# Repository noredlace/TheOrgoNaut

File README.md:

# TheOrgoNaut66

A design by u/lizardsticks

A an ergonomic ortholinear 60% board. Inspiration from the atreus with a twist on the modifiers and keys to fit most keycap designs. <br /> 

Nonstandard keycaps include the 2.25u Novelty on the left side. This keycap is meant to be used with either the Enter Key or a Novelty Enter Key. 

The left shift key was chosen to be a 2.75u with the right shift being a split shift 1.75u + 1u key.

I suppose the inner column 1u keycaps for 5,3 nd 5,4 could potentially be difficult to find, in the meantime the numpad of a keycap set should suffice.

This allows the keyboard to be symmetrical while having good compatibility with most base keycap sets.

KLE

The color code helps identify the rows of diodes that will be used. The spacing allows for me to visualize the columns. The actual PCB won't have the spacing that you see on the left and right side. The triangle spacing in the middle will stay.

Before this, I had made the matrix based off the position of keys, which made tracing messy due to a multitude of crossed traces. Thus I made necessary changes to allow for cleaner traces and minimal vias.

You can also see the row and column numbers to visualize the schematic.

Schematic was done in a 9 x 8 layout. This is due to the 66 keys on the OrgoNaut. <br />

PCB Dimensions are 148x362mm(5.81x14.25 inches) 
Front PCB

Back PCB

As you can see in the photos, the pcb is relatively clean in terms of the tracing. Of course its relative to how much of a mess my previous trace attempts have been.

Update v2 attempted to create aesthetically pleasing tracing. significant focus on how tracing to the pro micro 

Update v3 changed the pictures from KiCad's renderer to a gerber viewer provided by EasyEDA

Update v4 brought uniform ground planes to cover both front and back of the pcb. As well as changing the through hole footprints from m2 screw holes to pok3r style holes

# Major Update
The PCBs have been ordered and delivered courtesy of EasyEDA. The PCBs have been tested and all holes are currently registering correct keystrokes for the simple keyboard layout that has been made.

PCBs just delivered

PCB Soldered with diodes and socketed pro micro

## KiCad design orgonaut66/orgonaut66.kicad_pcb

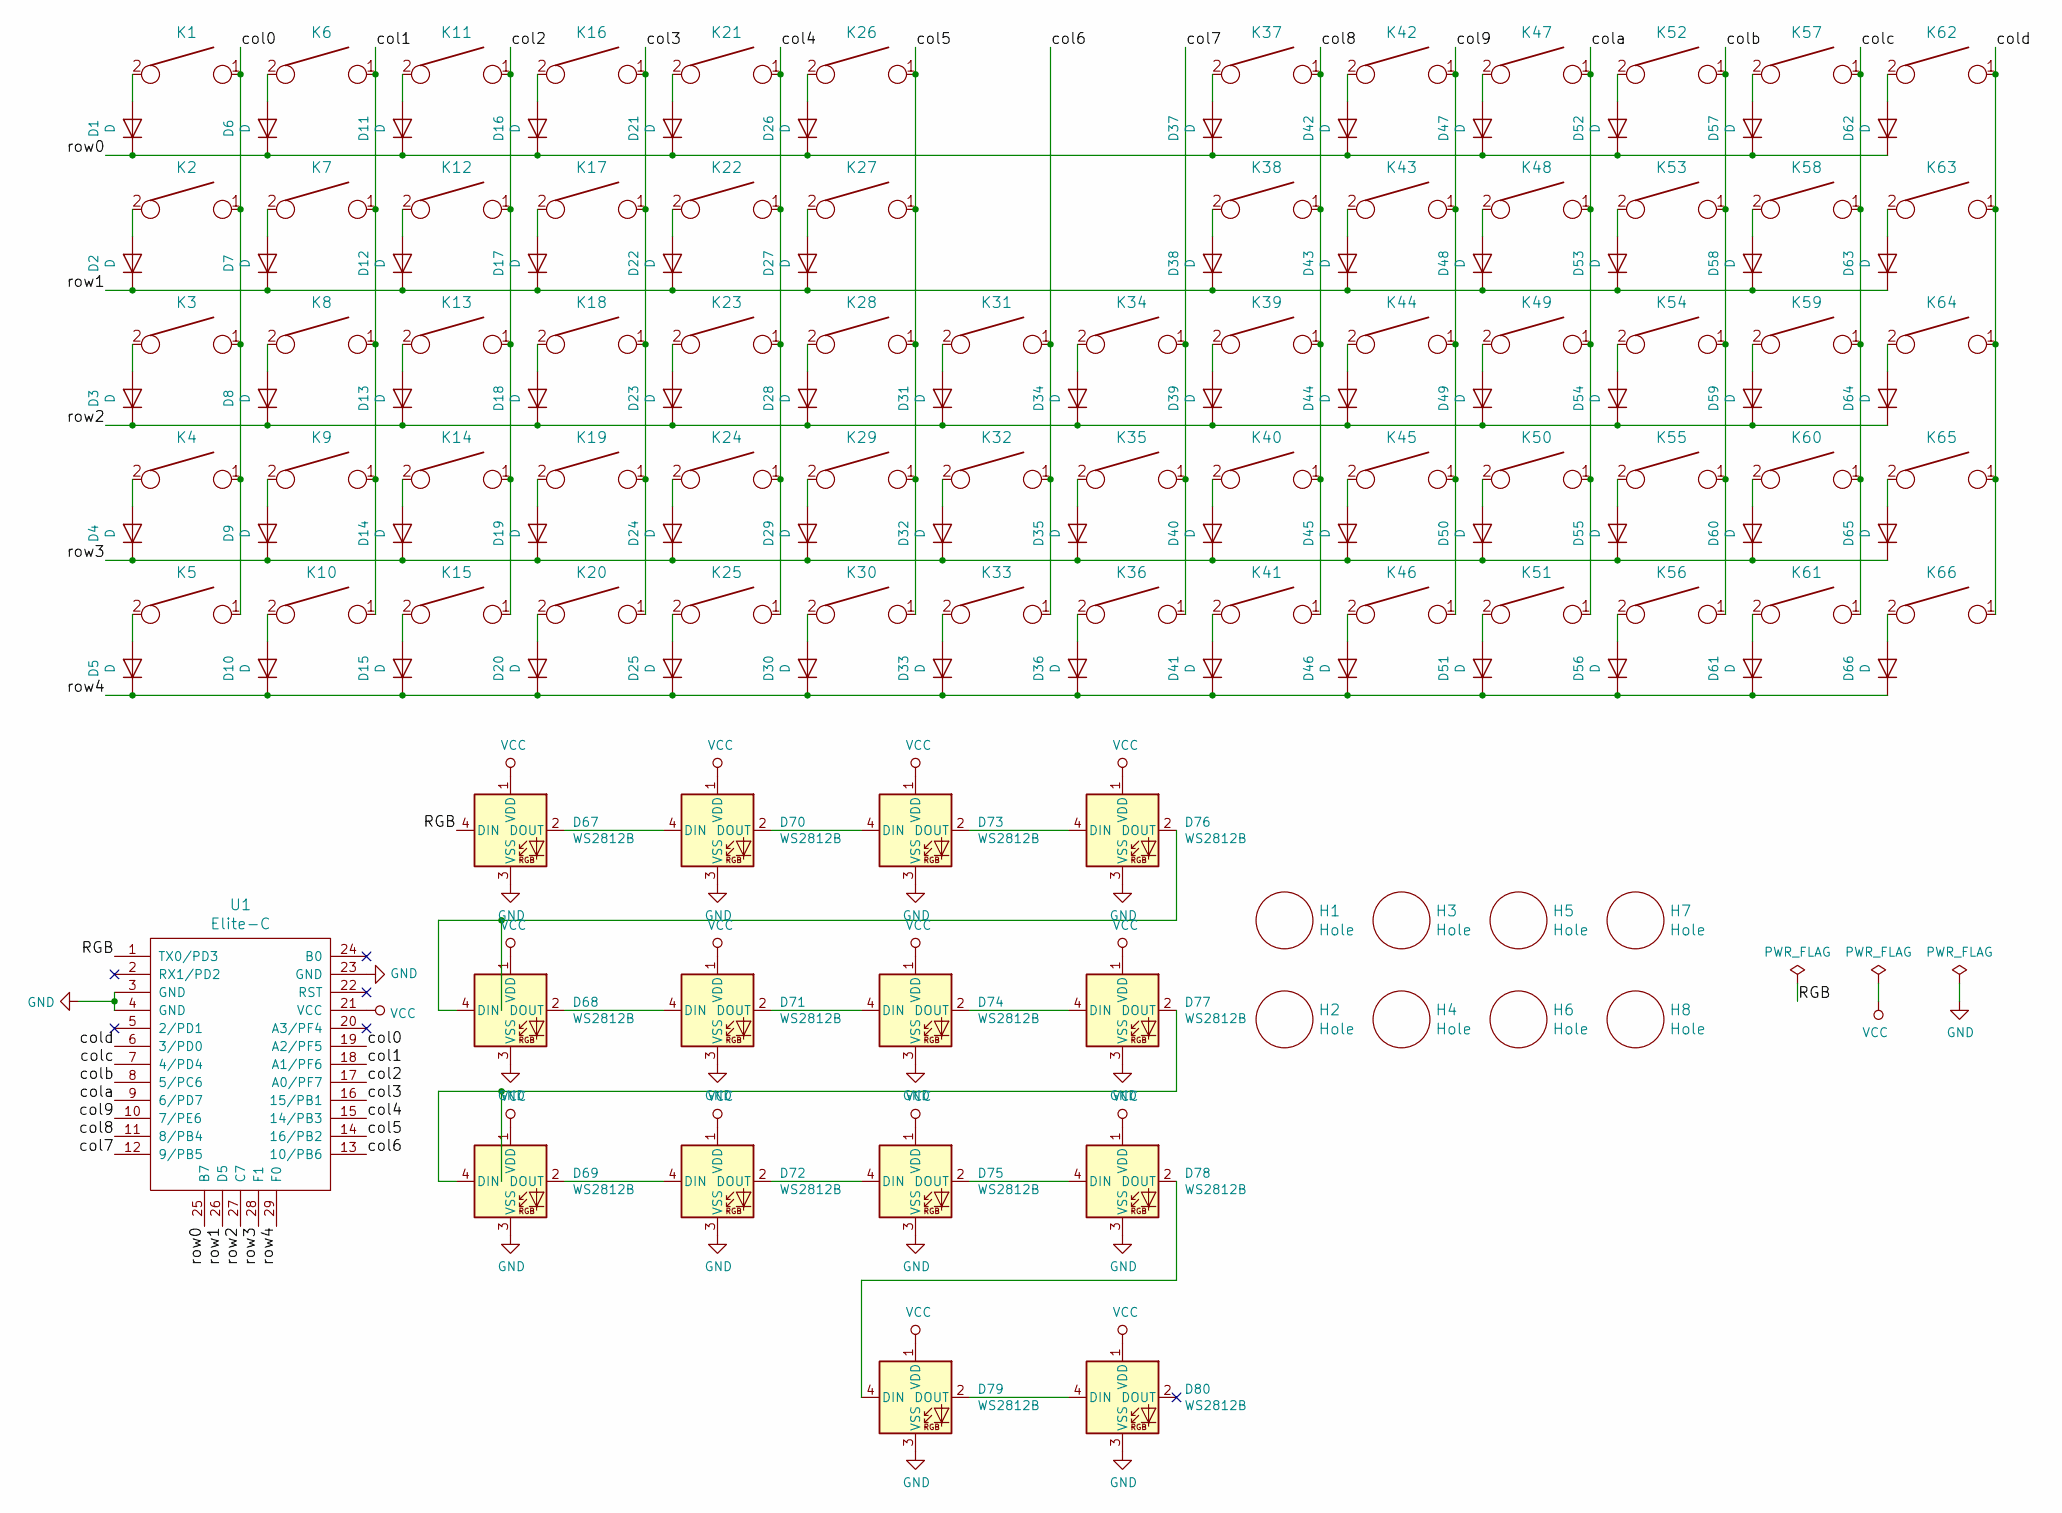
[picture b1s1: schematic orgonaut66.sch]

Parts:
D1, D2, D3, D4, D5, D6, D7, D8, D9, D10, D11, D12, D13, D14, D15, D16, D17, D18, D19, D20, D21, D22, D23, D24, D25, D26, D27, D28, D29, D30, D31, D32, D33, D34, D35, D36, D37, D38, D39, D40, D41, D42, D43, D44, D45, D46, D47, D48, D49, D50, D51, D52, D53, D54, D55, D56, D57, D58, D59, D60, D61, D62, D63, D64, D65, D66: D; D_SOD123_ThroughHole
D67, D68, D69, D70, D71, D72, D73, D74, D75, D76, D77, D78, D79, D80: WS2812B; RGBW_LED_5mm
H1, H2, H3, H4, H5, H6, H7, H8: Hole; Poker_oval_hole
K1, K2, K6, K7, K8, K9, K10, K11, K12, K13, K14, K15, K16, K17, K18, K19, K20, K21, K22, K23, K24, K25, K26, K27, K28, K29, K30, K31, K32, K34, K35, K37, K38, K39, K40, K41, K42, K43, K44, K45, K46, K47, K48, K49, K50, K51, K52, K53, K54, K55, K56, K57, K58, K59, K60, K61, K66: KEYSW; Mx_Alps_100
K3, K63: KEYSW; Mx_Alps_150
K4, K64: KEYSW; Mx_Alps_225
K5: KEYSW; Mx_Alps_275
K33, K36: KEYSW; Mx_Alps_200-dualside
K62: KEYSW; Mx_Alps_200
K65: KEYSW; Mx_Alps_175
U1: Elite-C; Elite-C-ZigZag

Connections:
/RGB: D67.4 (DIN), U1.1 (TX0/PD3)
/col0: K1.1, K2.1, K3.1, K4.1, K5.1, U1.19 (A2/PF5)
/col1: K6.1, K7.1, K8.1, K9.1, K10.1, U1.18 (A1/PF6)
/col2: K11.1, K12.1, K13.1, K14.1, K15.1, U1.17 (A0/PF7)
/col3: K16.1, K17.1, K18.1, K19.1, K20.1, U1.16 (15/PB1)
/col4: K21.1, K22.1, K23.1, K24.1, K25.1, U1.15 (14/PB3)
/col5: K26.1, K27.1, K28.1, K29.1, K30.1, U1.14 (16/PB2)
/col6: K31.1, K32.1, K33.1, U1.13 (10/PB6)
/col7: K34.1, K35.1, K36.1, U1.12 (9/PB5)
/col8: K37.1, K38.1, K39.1, K40.1, K41.1, U1.11 (8/PB4)
/col9: K42.1, K43.1, K44.1, K45.1, K46.1, U1.10 (7/PE6)
/cola: K47.1, K48.1, K49.1, K50.1, K51.1, U1.9 (6/PD7)
/colb: K52.1, K53.1, K54.1, K55.1, K56.1, U1.8 (5/PC6)
/colc: K57.1, K58.1, K59.1, K60.1, K61.1, U1.7 (4/PD4)
/cold: K62.1, K63.1, K64.1, K65.1, K66.1, U1.6 (3/PD0)
/row0: D1.1 (K), D6.1 (K), D11.1 (K), D16.1 (K), D21.1 (K), D26.1 (K), D37.1 (K), D42.1 (K), D47.1 (K), D52.1 (K), D57.1 (K), D62.1 (K), U1.25 (B7)
/row1: D2.1 (K), D7.1 (K), D12.1 (K), D17.1 (K), D22.1 (K), D27.1 (K), D38.1 (K), D43.1 (K), D48.1 (K), D53.1 (K), D58.1 (K), D63.1 (K), U1.26 (D5)
/row2: D3.1 (K), D8.1 (K), D13.1 (K), D18.1 (K), D23.1 (K), D28.1 (K), D31.1 (K), D34.1 (K), D39.1 (K), D44.1 (K), D49.1 (K), D54.1 (K), D59.1 (K), D64.1 (K), U1.27 (C7)
/row3: D4.1 (K), D9.1 (K), D14.1 (K), D19.1 (K), D24.1 (K), D29.1 (K), D32.1 (K), D35.1 (K), D40.1 (K), D45.1 (K), D50.1 (K), D55.1 (K), D60.1 (K), D65.1 (K), U1.28 (F1)
/row4: D5.1 (K), D10.1 (K), D15.1 (K), D20.1 (K), D25.1 (K), D30.1 (K), D33.1 (K), D36.1 (K), D41.1 (K), D46.1 (K), D51.1 (K), D56.1 (K), D61.1 (K), D66.1 (K), U1.29 (F0)
GND: D67.3 (VSS), D68.3 (VSS), D69.3 (VSS), D70.3 (VSS), D71.3 (VSS), D72.3 (VSS), D73.3 (VSS), D74.3 (VSS), D75.3 (VSS), D76.3 (VSS), D77.3 (VSS), D78.3 (VSS), D79.3 (VSS), D80.3 (VSS), U1.3 (GND), U1.4 (GND), U1.23 (GND)
unnamed: D1.2 (A), K1.2
unnamed: D2.2 (A), K2.2
unnamed: D3.2 (A), K3.2
unnamed: D4.2 (A), K4.2
unnamed: D5.2 (A), K5.2
unnamed: D6.2 (A), K6.2
unnamed: D7.2 (A), K7.2
unnamed: D8.2 (A), K8.2
unnamed: D9.2 (A), K9.2
unnamed: D10.2 (A), K10.2
unnamed: D11.2 (A), K11.2
unnamed: D12.2 (A), K12.2
unnamed: D13.2 (A), K13.2
unnamed: D14.2 (A), K14.2
unnamed: D15.2 (A), K15.2
unnamed: D16.2 (A), K16.2
unnamed: D17.2 (A), K17.2
unnamed: D18.2 (A), K18.2
unnamed: D19.2 (A), K19.2
unnamed: D20.2 (A), K20.2
unnamed: D21.2 (A), K21.2
unnamed: D22.2 (A), K22.2
unnamed: D23.2 (A), K23.2
unnamed: D24.2 (A), K24.2
unnamed: D25.2 (A), K25.2
unnamed: D26.2 (A), K26.2
unnamed: D27.2 (A), K27.2
unnamed: D28.2 (A), K28.2
unnamed: D29.2 (A), K29.2
unnamed: D30.2 (A), K30.2
unnamed: D31.2 (A), K31.2
unnamed: D32.2 (A), K32.2
unnamed: D33.2 (A), K33.2
unnamed: D34.2 (A), K34.2
unnamed: D35.2 (A), K35.2
unnamed: D36.2 (A), K36.2
unnamed: D37.2 (A), K37.2
unnamed: D38.2 (A), K38.2
unnamed: D39.2 (A), K39.2
unnamed: D40.2 (A), K40.2
unnamed: D41.2 (A), K41.2
unnamed: D42.2 (A), K42.2
unnamed: D43.2 (A), K43.2
unnamed: D44.2 (A), K44.2
unnamed: D45.2 (A), K45.2
unnamed: D46.2 (A), K46.2
unnamed: D47.2 (A), K47.2
unnamed: D48.2 (A), K48.2
unnamed: D49.2 (A), K49.2
unnamed: D50.2 (A), K50.2
unnamed: D51.2 (A), K51.2
unnamed: D52.2 (A), K52.2
unnamed: D53.2 (A), K53.2
unnamed: D54.2 (A), K54.2
unnamed: D55.2 (A), K55.2
unnamed: D56.2 (A), K56.2
unnamed: D57.2 (A), K57.2
unnamed: D58.2 (A), K58.2
unnamed: D59.2 (A), K59.2
unnamed: D60.2 (A), K60.2
unnamed: D61.2 (A), K61.2
unnamed: D62.2 (A), K62.2
unnamed: D63.2 (A), K63.2
unnamed: D64.2 (A), K64.2
unnamed: D65.2 (A), K65.2
unnamed: D66.2 (A), K66.2
unnamed: D67.2 (DOUT), D70.4 (DIN)
unnamed: D68.2 (DOUT), D71.4 (DIN)
unnamed: D68.4 (DIN), D76.2 (DOUT)
unnamed: D69.2 (DOUT), D72.4 (DIN)
unnamed: D69.4 (DIN), D77.2 (DOUT)
unnamed: D70.2 (DOUT), D73.4 (DIN)
unnamed: D71.2 (DOUT), D74.4 (DIN)
unnamed: D72.2 (DOUT), D75.4 (DIN)
unnamed: D73.2 (DOUT), D76.4 (DIN)
unnamed: D74.2 (DOUT), D77.4 (DIN)
unnamed: D75.2 (DOUT), D78.4 (DIN)
unnamed: D78.2 (DOUT), D79.4 (DIN)
unnamed: D79.2 (DOUT), D80.4 (DIN)
VCC: D67.1 (VDD), D68.1 (VDD), D69.1 (VDD), D70.1 (VDD), D71.1 (VDD), D72.1 (VDD), D73.1 (VDD), D74.1 (VDD), D75.1 (VDD), D76.1 (VDD), D77.1 (VDD), D78.1 (VDD), D79.1 (VDD), D80.1 (VDD), U1.21 (VCC)

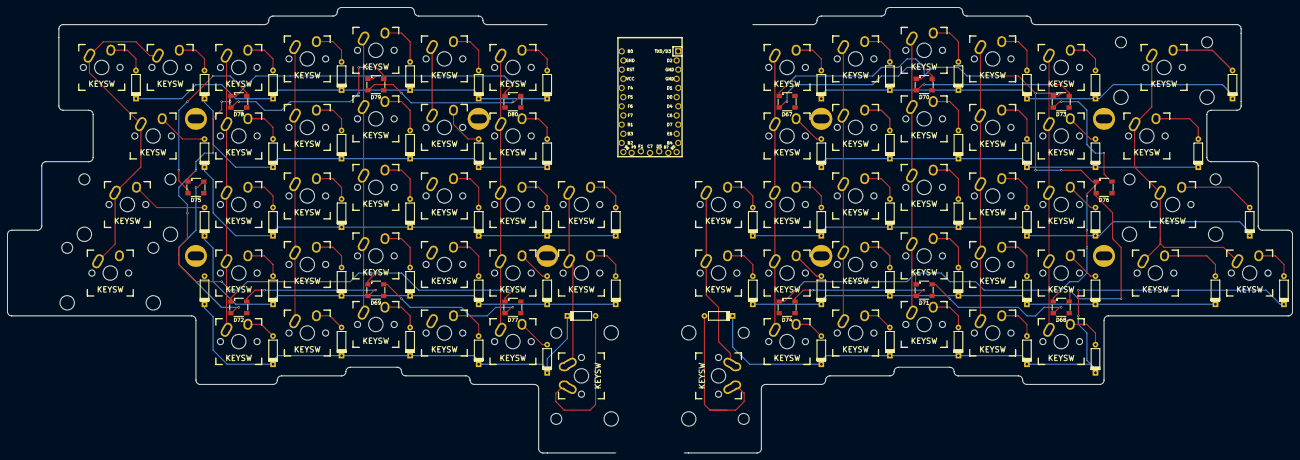
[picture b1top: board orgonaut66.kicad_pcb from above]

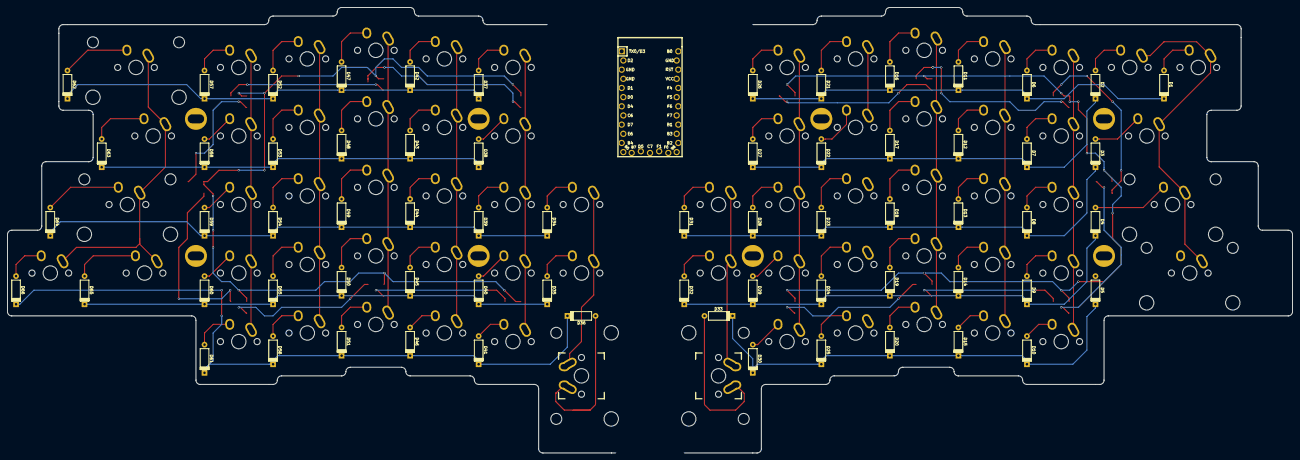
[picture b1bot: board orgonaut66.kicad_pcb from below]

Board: 2 copper layers, 356.2 x 123.5 mm, 155 parts (67 on the bottom side), 101 nets.

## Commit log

2018-09-06 push beginning of orgonaut 66 pcb
2018-09-07 finsh tracing
2018-09-07 modify tracings & add gerber
2018-09-07 update gerber
2018-09-07 clean up pcb, update gerber
2018-09-07 push v2 changes
2018-09-07 update readme photos
2018-09-08 add standard layout picture
2018-09-08 new gerber
2018-09-11 update step
2018-09-12 push new gerber/ reroute space
2018-09-12 rename pics
2018-09-12 redo gerber
2018-09-12 update save
2018-09-21 update bottom ground plane
2018-09-22 modify ground planes, change holes to pok3r
2018-09-22 push
2018-09-22 push new pcb pictures
2018-09-22 readme
2018-09-22 rename from png to jpg
2018-09-22 r e a d m e
2018-09-25 update pcb
2018-10-18 idk what this commit is, new gerbers?
2018-12-03 get dxf files
2018-12-03 generate step and dxf files for case design
2018-12-04 push switch clearance
2019-07-30 update steps/design files
2019-07-30 update orgonaut v4 for elite c
